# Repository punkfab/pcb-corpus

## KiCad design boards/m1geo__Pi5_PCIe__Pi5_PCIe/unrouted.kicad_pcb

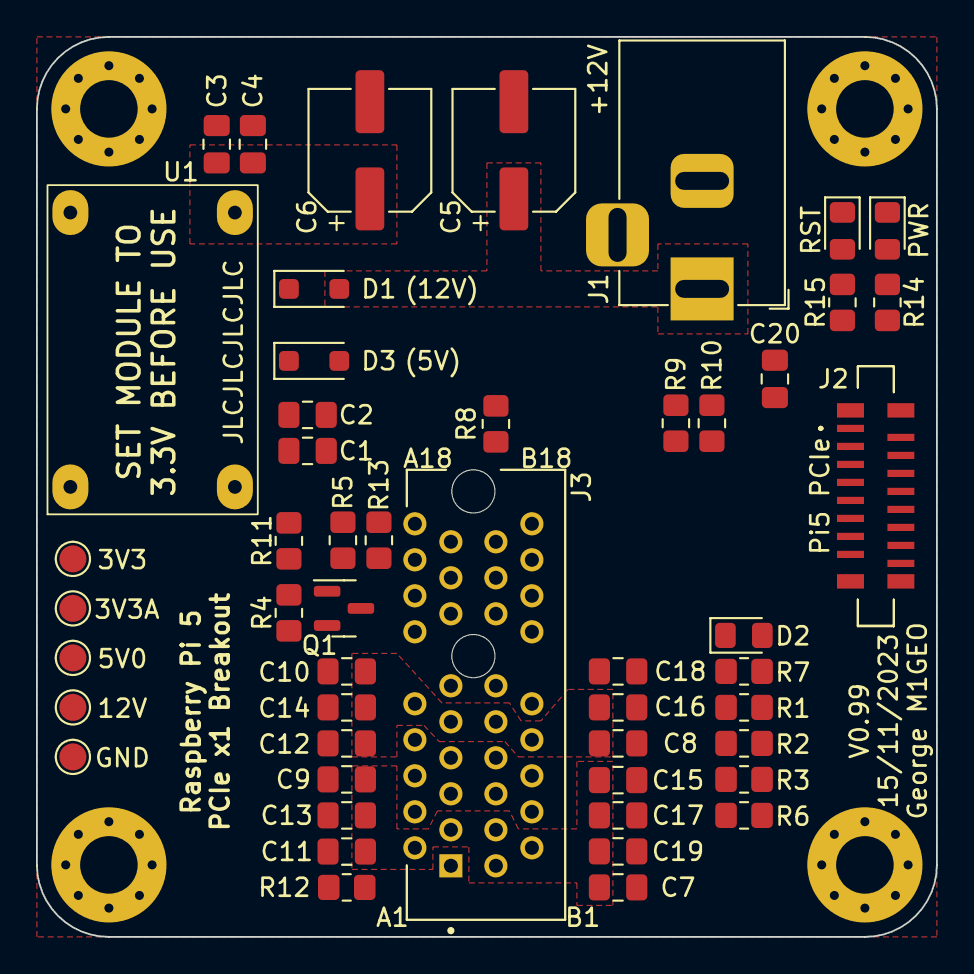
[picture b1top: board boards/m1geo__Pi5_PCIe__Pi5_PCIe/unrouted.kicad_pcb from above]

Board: 4 copper layers, 50.0 x 50.0 mm, 54 parts (0 on the bottom side), 24 nets, no tracks yet.

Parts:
C1, C3, C11, C12, C13, C14, C15, C16, C17, C18, C19, C20: 100n; C_0805_2012Metric_Pad1.18x1.45mm_HandSolder
C2, C4, C7, C8, C9, C10: 10u; C_0805_2012Metric_Pad1.18x1.45mm_HandSolder
C5, C6: 150u; CP_Elec_6.3x7.7
D1: (12V); D_SOD-123F
D2: DNF; D_0805_2012Metric_Pad1.15x1.40mm_HandSolder
D3: (5V); D_SOD-123F
D4: PWR; LED_0805_2012Metric_Pad1.15x1.40mm_HandSolder
D5: RST; LED_0805_2012Metric_Pad1.15x1.40mm_HandSolder
H1, H2, H3, H4: MountingHole_Pad; MountingHole_3.2mm_M3_Pad_Via
J1: 12V IN; BarrelJack_Horizontal
J2: Pi5 PCIe; 687316124422
J3: 10018783-11200TLF; AMPHENOL_10018783-11200TLF
Q1: BS170F; SOT-23
R1, R2, R3: DNF; R_0805_2012Metric_Pad1.20x1.40mm_HandSolder
R4, R6, R7, R8, R9, R10, R13: 10k; R_0805_2012Metric_Pad1.20x1.40mm_HandSolder
R5, R11, R12: 0; R_0805_2012Metric_Pad1.20x1.40mm_HandSolder
R14, R15: 1k; R_0805_2012Metric_Pad1.20x1.40mm_HandSolder
TP1: 3V3; TestPoint_Pad_D1.5mm
TP2: 3V3A; TestPoint_Pad_D1.5mm
TP3: 5V0; TestPoint_Pad_D1.5mm
TP4: 12V; TestPoint_Pad_D1.5mm
TP5: GND; TestPoint_Pad_D1.5mm
U1: Mini360; Mini360_step-down

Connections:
+3.3VA: C18.1, J3.B10, R6.2, R7.2, R8.2, R9.2, R10.2, R11.1, R13.2, TP2.1
+3V3: C3.1, C4.1, C6.1, C8.1, C10.1, C12.1, C14.1, C16.1, J3.A9, J3.A10, J3.B8, R11.2, R14.1, TP1.1, U1.4 (OUT+)
+5V: C20.1, D3.2 (A), J2.15 (Pin_17), J2.16 (Pin_18), TP3.1
+12V: C5.1, C7.1, C9.1, C11.1, C13.1, C15.1, C17.1, C19.1, D1.2 (A), J1.1, J3.A2, J3.A3, J3.B1, J3.B2, J3.B3, TP4.1
/PRSNT1#: J3.A1, R12.1
/REG_IN: C1.1, C2.1, D1.1 (K), D3.1 (K), U1.2 (IN+)
GND: C1.2, C2.2, C3.2, C4.2, C5.2, C6.2, C7.2, C8.2, C9.2, C10.2, C11.2, C12.2, C13.2, C14.2, C15.2, C16.2, C17.2, C18.2, C19.2, C20.2, D4.1 (K), D5.1 (K), H1.1, H2.1, H3.1, H4.1, J1.2, J1.3, J2.5 (Pin_7), J2.8 (Pin_10), J2.11 (Pin_13), J2.14 (Pin_16), J2.MP1, J2.MP2, J2.MP3, J2.MP4, J3.A4, J3.A12, J3.A15, J3.A18, J3.B4, J3.B7, J3.B13, J3.B16, J3.B18, Q1.2 (S), R4.2, R12.2, TP5.1, U1.1 (IN-), U1.3 (OUT-)
unnamed: D4.2 (A), R14.2
unnamed: D5.2 (A), R15.2
unnamed: Q1.1 (G), R4.1, R5.1
PCIE_CLKN: J2.12 (Pin_14), J3.A14
PCIE_CLKP: J2.13 (Pin_15), J3.A13
PCIE_CLKREQ#: J3.B12, R3.1, R6.1
PCIE_PERST#: J3.A11, Q1.3 (D), R13.1
PCIE_PRSNT2#: J3.B17, R2.1, R8.1
PCIE_RX0N: J2.9 (Pin_11), J3.A17
PCIE_RX0P: J2.10 (Pin_12), J3.A16
PCIE_SMCLK: J2.4 (Pin_6), J3.B5, R9.1
PCIE_SMDAT: D2.2 (A), J2.3 (Pin_5), J3.B6, R10.1
PCIE_TX0N: J2.6 (Pin_8), J3.B15
PCIE_TX0P: J2.7 (Pin_9), J3.B14
PCIE_WAKE#: D2.1 (K), J3.B11, R1.1, R7.1
RESET: J2.1 (Pin_3), R5.2, R15.1
UNKNOWN?!: J2.2 (Pin_4), R1.2, R2.2, R3.2

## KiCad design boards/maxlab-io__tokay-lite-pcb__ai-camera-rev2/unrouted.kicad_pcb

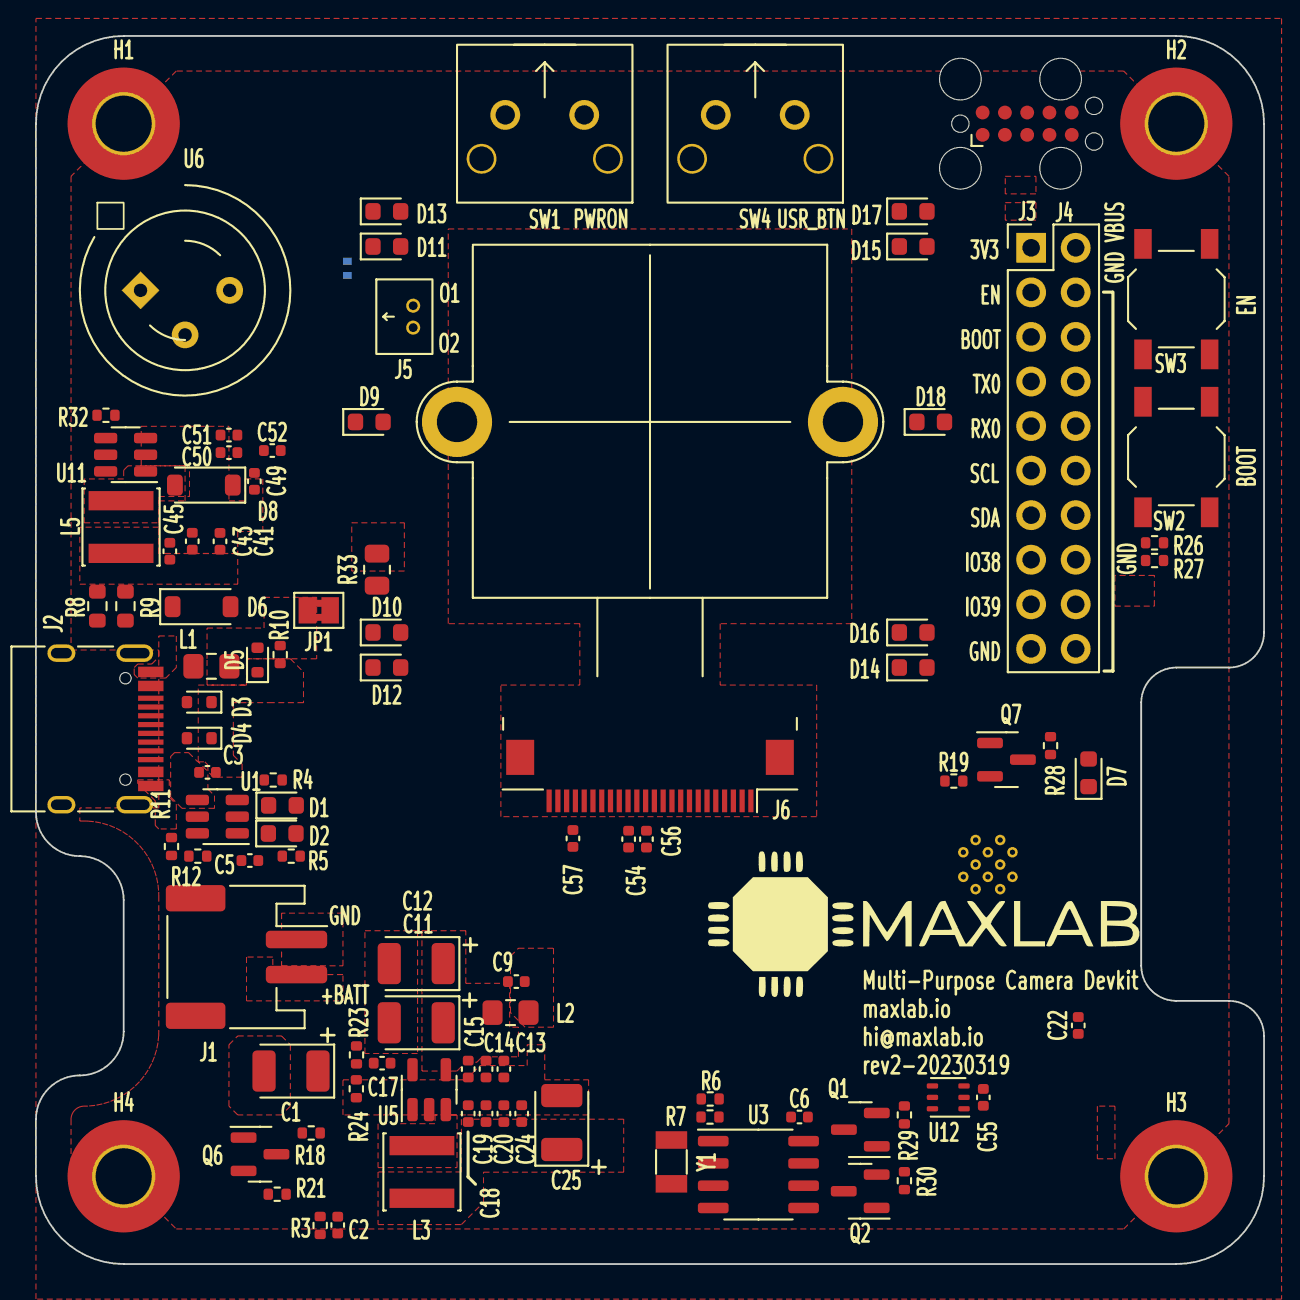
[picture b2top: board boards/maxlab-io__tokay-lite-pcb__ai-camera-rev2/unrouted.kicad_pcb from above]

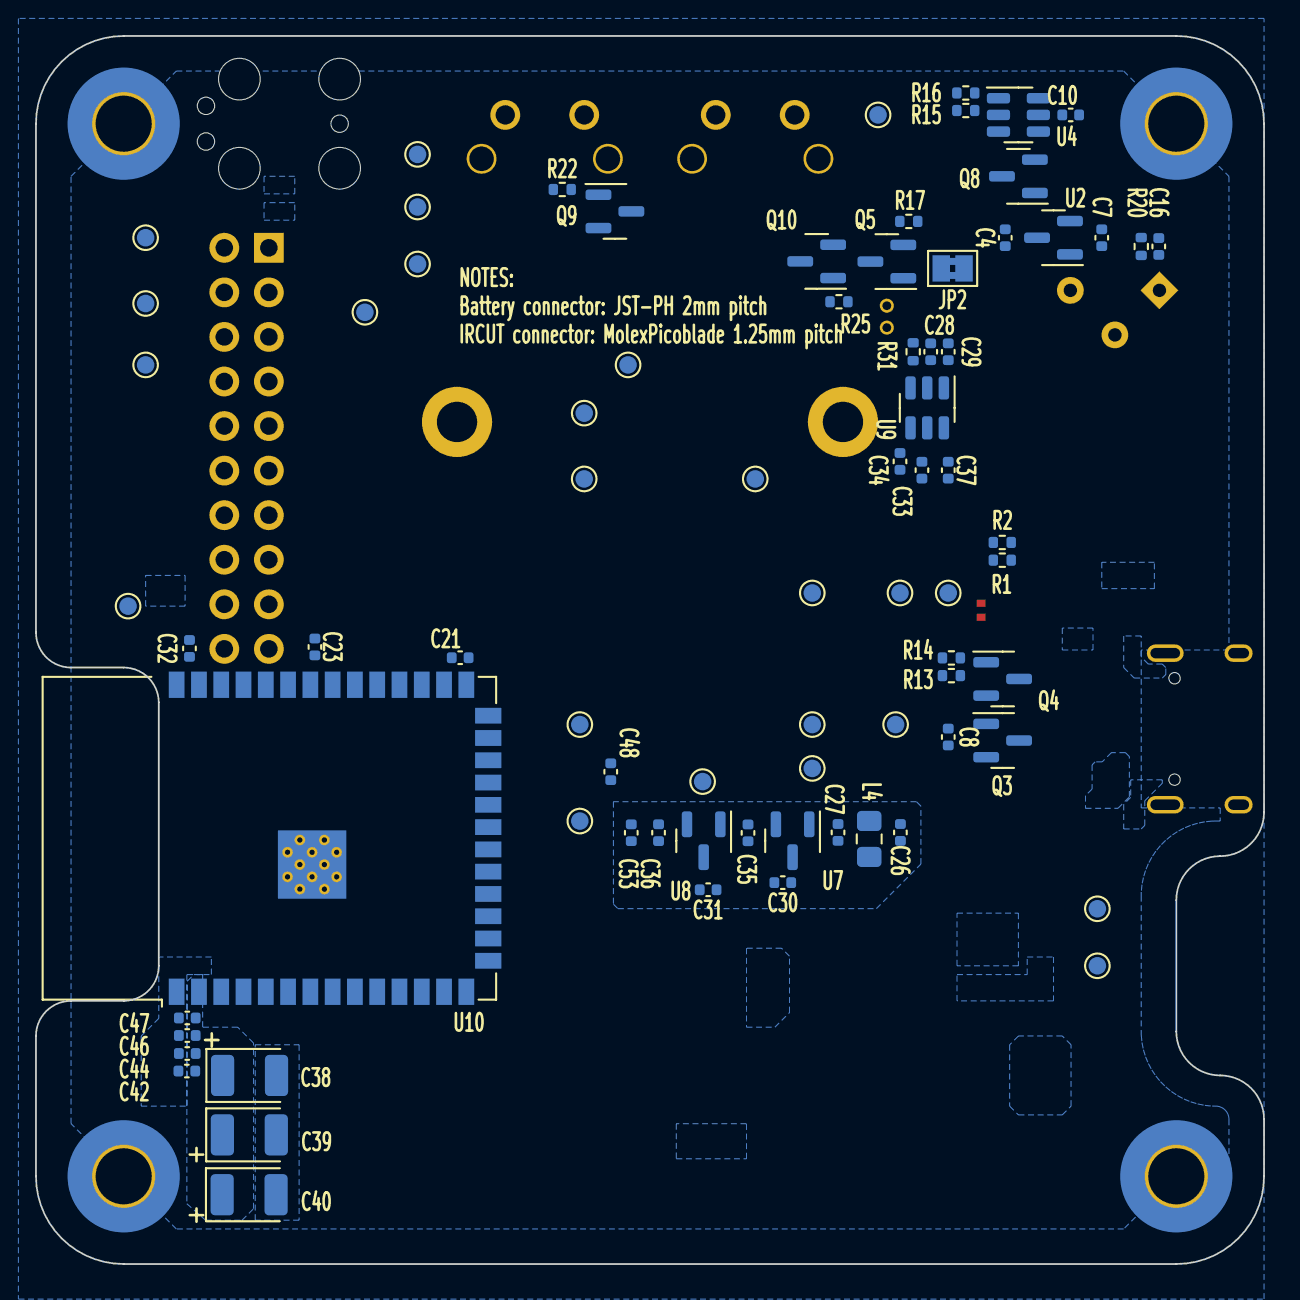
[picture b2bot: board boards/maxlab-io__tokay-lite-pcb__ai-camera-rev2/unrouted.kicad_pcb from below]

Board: 4 copper layers, 70.0 x 70.0 mm, 176 parts (77 on the bottom side), 84 nets, no tracks yet.

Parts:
C1, C11, C12, C25, C38, C39, C40: 100u_CASE-B-3528_TAJB107K006RNJ; CP_EIA-3528-15_AVX-H
C2, C3, C4, C5, C6, C7, C8, C9, C10, C13, C14, C15, C16, C18, C19, C20, C21, C22, C23, C24, C26, C27, C28, C29, C30, C31, C32, C33, C34, C35, C36, C37, C41, C42, C43, C44, C45, C46, C47, C49, C50, C51, C52, C53, C54, C55, C56, C57: 10u_0402_CL05A105KA5NQNC; C_0402_1005Metric
C17, C48: 22p_0402_0402CG220J500NT; C_0402_1005Metric
D1, D7: 0603_RED_KT-0603R; LED_0603_1608Metric
D2: 0603_GREEN_19-217/GHC-YR1S2/3T; LED_0603_1608Metric
D3, D4, D5: SOD-523_BSD5C051L; D_SOD-523
D6, D8: B5819W-SL_SOD-123; D_SOD-123
D9, D10, D11, D12, D13, D14, D15, D16, D17, D18: 0603_IR_850nm_E6C0603IRAC1UDA; LED_0603_1608Metric
H1, H2, H3, H4: MountingHole_Pad; MountingHole_3.2mm_M3_Pad_TopBottom
J1: Conn-01x02_P2mm_NONAME_JST-PH_C47647; JST_PH_S2B-PH-SM4-TB_1x02-1MP_P2.00mm_Horizontal
J2: TYPE-C-31-M-12; USB_C_Receptacle_HRO_TYPE-C-31-M-12
J3: MAXLAB; Tag-Connect_TC2050-IDC-FP_2x05_P1.27mm_Vertical
J4: Conn-02x10_P2.54mm_B-2100S20P-B110; PinHeader_2x10_P2.54mm_Vertical
J5: Conn-01x02_P1.25mm_10114829-10102LF; 10114829-10102LF
J6: Conn_01x24_FFC_0.5mm_AFC01-S24FCC-00; Jushuo_AFC01-S24FCC-00_1x24-1MP_P0.50_Horizontal
JP1: USB_PWR; SolderJumper-2_P1.3mm_Bridged2Bar_Pad1.0x1.5mm
JP2: PIR; SolderJumper-2_P1.3mm_Bridged2Bar_Pad1.0x1.5mm
L1, L2, L4: 0805_FB_220R@100MHz_BLM21PG221SN1D; L_0805_2012Metric_Pad1.15x1.40mm_HandSolder
L3, L5: 10u_SWPA4030S100MT; L_Sunlord_SWPA40xxS
Q1, Q2, Q5, Q7, Q9, Q10: 2N7002; SOT-23
Q3, Q4, Q6, Q8: AO3401A; SOT-23
R1, R2, R23: 976k_0402_0402WGD9763TCE; R_0402_1005Metric
R3, R13, R15, R16, R17, R18, R19, R21, R22, R24, R25, R31, R32: 215k_0402_0402WGD2153TCE; R_0402_1005Metric
R4, R5, R28: 1k_0402_0402WGF1001TCE; R_0402_1005Metric
R6, R7, R10, R11, R12, R14, R20, R26, R27, R29, R30: 10k_0402_0402WGF1002TCE; R_0402_1005Metric
R8, R9: 5.1k_0603_0603WAF5101T5E; R_0603_1608Metric
R33: 2.43R_0805_0805W8F243KT5E; R_0805_2012Metric
SW1, SW4: SW_PB_90deg_K2-1102AQ-H4CW-01
SW2, SW3: SW_PB_TS-1187A-B-A-B; SW_SPST_TL3342
TP1, TP2, TP3, TP4, TP5, TP6, TP7, TP8, TP9, TP10, TP11, TP12, TP13, TP14, TP15, TP16, TP17, TP18, TP19, TP20, TP21, TP22, TP23, TP24: TestPoint; TestPoint_Pad_D1.0mm
U1: TP4057-42-SOT26-R; SOT-23-6
U2, U7: XC6206-2.8V; SOT-23
U3: PCF85063AT_SO8; SO-8_3.9x4.9mm_P1.27mm
U4: SOT-23-6_SN74LVC1G373DBVR_TI; SOT-23-6
U5: SY8089AAAC; SOT-23-5
U6: PIR_AS312; AS312
U8: RT9166-12GVL; SOT-23
U9: AP1511B; SOT-23-6
U10: ESP32-S3-WROOM-1-N16R8; ESP32-S3-WROOM-1
U11: MT9284-28J; SOT-23-6
U12: LTR-303ALS-01; Lite-On_LTR-303ALS-01
Y1: 32.768kHz_Q13FC1350000400; Crystal_SMD_3215-2Pin_3.2x1.5mm

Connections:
+1V2: C36.1, C54.2, J6.15, TP16.1, U8.2 (VO)
+2V8: C35.1, C57.2, J6.21, TP18.1, U7.2 (VO)
+3.3VA: C27.1, C30.1, C31.1, C53.1, C56.2, J6.14, L4.2, U7.3 (VI), U8.3 (VI)
+3V3: C17.1, C18.2, C19.2, C20.2, C24.2, C25.1, C26.1, C33.2, C34.2, C37.2, C38.1, C39.1, C40.1, C42.1, C44.1, C46.1, C47.1, C55.1, J3.2, J4.1, L3.2, L4.1, Q1.1 (G), Q2.1 (G), R23.1, R26.2, R27.2, R29.1, R30.1, TP22.1, U9.5 (VDD), U10.2 (3V3), U12.1 (VDD)
+5V: C3.2, D5.2 (A2), JP1.2 (B), L1.2, R4.1, R5.1, R10.1, TP23.1, U1.4 (V_{cc})
+BATT: C1.1, C5.1, J1.2, Q3.3 (D), R1.1, TP19.1, U1.3 (BAT)
/BATT_DETECT: C32.1, R1.2, R2.1, TP11.1, U10.39 (GPIO1/TOUCH1/ADC1_CH0)
/CAM.D2: J6.6, U10.7 (GPIO7/TOUCH7/ADC1_CH6)
/CAM.D3: J6.4, U10.5 (GPIO5/TOUCH5/ADC1_CH4)
/CAM.D4: J6.3, U10.4 (GPIO4/TOUCH4/ADC1_CH3)
/CAM.D5: J6.5, U10.6 (GPIO6/TOUCH6/ADC1_CH5)
/CAM.D6: J6.7, U10.8 (GPIO15/U0RTS/ADC2_CH4/XTAL_32K_P)
/CAM.D7: J6.9, U10.10 (GPIO17/U1TXD/ADC2_CH6)
/CAM.D8: J6.11, U10.11 (GPIO18/U1RXD/ADC2_CH7/CLK_OUT3)
/CAM.D9: J6.13, U10.20 (GPIO12/TOUCH12/ADC2_CH1/FSPICLK/FSPIIO6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)
/CAM.HREF: J6.16, U10.33 (MTDO/GPIO40/CLK_OUT2)
/CAM.MCLK: J6.12, U10.12 (GPIO8/TOUCH8/ADC1_CH7/SUBSPICS1)
/CAM.PCLK: C48.1, J6.8, U10.9 (GPIO16/U0CTS/ADC2_CH5/XTAL_32K_NH5)
/CAM.PWDN: J6.17, U10.17 (GPIO9/TOUCH9/ADC1_CH8/FSPIHD/SUBSPIHD)
/CAM.RST: J6.19, U10.19 (GPIO11/TOUCH11/ADC2_CH0/FSPID/FSPIIO5/S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)
/CAM.SCL: J4.11, J6.20, Q1.2 (S), R29.2, U10.15 (GPIO3/TOUCH3/ADC1_CH2), U12.4 (SCL)
/CAM.SDA: J4.13, J6.22, Q2.2 (S), R30.2, U10.21 (GPIO13/TOUCH13/ADC2_CH2/FSPIQ/FSPIIO7/S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), U12.6 (SDA)
/CAM.VSYNC: J6.18, U10.18 (GPIO10/TOUCH10/ADC1_CH9/FSPICS0/FSPIIO4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)
/ESP_BOOT: C21.2, J3.6, J4.5, R26.1, SW2.2, TP2.1, U10.27 (GPIO0/BOOT)
/ESP_EN: C22.2, J3.5, J4.3, R27.1, SW3.2, TP1.1, U10.3 (EN)
/IO38: J4.15, U10.31 (GPIO38/FSPIWP/SUBSPIWP)
/IO39: J4.17, U10.32 (MTCK/GPIO39/CLK_OUT3/SUBSPICS1)
/IRCUT_CTRL: R31.2, TP10.1, U9.3 (FBC), U10.25 (GPIO48/SPICLK_N/SUBSPICLK_N_DIFF)
/IRLED_PWM: R32.2, TP14.1, U10.16 (GPIO46), U11.4 (EN)
/PIR_CTRL_D: R15.2, TP8.1, U4.3 (D), U10.23 (GPIO21)
/PIR_CTRL_LE: R16.2, TP7.1, U4.1 (LE), U10.26 (GPIO45)
/PIR_OUT: Q10.3 (D), U10.24 (GPIO47/SPICLK_P/SUBSPICLK_P_DIFF)
/PWRON_DET: Q9.1 (G), R22.2, SW1.2, U10.38 (GPIO2/TOUCH2/ADC1_CH1)
/PWR_EN: Q7.1 (G), R19.2, TP12.1, U10.22 (GPIO14/TOUCH14/ADC2_CH3/FSPIWP/FSPIDQS/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)
/PWR_PIR: C7.1, C10.1, C16.1, R20.1, SW1.1, TP13.1, U2.2 (VO), U4.5 (VCC), U6.1 (VDD)
/RXD0: J3.8, J4.9, TP5.1, U10.36 (U0RXD/GPIO44/CLK_OUT2)
/TXD0: J3.7, J4.7, TP4.1, U10.37 (U0TXD/GPIO43/CLK_OUT1)
/UD+: D4.2 (A2), J2.A6 (D+), J2.B6 (D+), U10.14 (GPIO20/U1CTS/ADC2_CH9/CLK_OUT1/USB_D+)
/UD-: D3.2 (A2), J2.A7 (D-), J2.B7 (D-), U10.13 (GPIO19/U1RTS/ADC2_CH8/CLK_OUT2/USB_D-)
/USR_BTN: C23.2, SW4.2, U10.34 (MTDI/GPIO41/CLK_OUT1)
/USR_LED: R28.1, U10.35 (MTMS/GPIO42)
GND: C1.2, C2.1, C3.1, C4.1, C5.2, C6.2, C7.2, C9.1, C10.2, C11.2, C12.2, C13.1, C14.2, C15.1, C16.2, C18.1, C19.1, C20.1, C21.1, C22.1, C23.1, C24.1, C25.2, C26.2, C27.2, C28.2, C29.2, C30.2, C31.2, C32.2, C33.1, C34.1, C35.2, C36.2, C37.1, C38.2, C39.2, C40.2, C41.1, C42.2, C43.2, C44.2, C45.1, C46.2, C47.2, C48.2, C49.2, C50.1, C51.1, C52.1, C53.2, C54.1, C55.2, C56.1, C57.1, D3.1 (A1), D4.1 (A1), D5.1 (A1), D7.1 (K), J1.1, J2.A1 (GND), J2.A12 (GND), J2.B1 (GND), J2.B12 (GND), J3.3, J3.4, J4.4, J4.6, J4.8, J4.10, J4.12, J4.14, J4.16, J4.18, J4.19, J4.20, J6.10, J6.23, Q5.2 (S), Q7.2 (S), Q9.2 (S), Q10.2 (S), R2.2, R3.2, R8.2, R9.2, R10.2, R11.2, R12.2, R13.2, R15.1, R16.1, R17.1, R19.1, R21.2, R22.1, R24.2, R25.1, R31.1, R32.1, R33.2, SW2.1, SW3.1, SW4.1, TP3.1, TP6.1, TP9.1, TP15.1, TP17.1, TP20.1, TP24.1, U1.2 (GND), U2.1 (GND), U3.4 (VSS), U4.2 (G), U4.6 (~OE), U5.2 (GND), U6.3 (VSS), U7.1 (GND), U8.1 (GND), U9.2 (GND), U10.1 (GND), U10.40 (GND), U10.41 (GND), U11.2 (GND), U12.3 (GND)
GNDPWR: C2.2, H1.1, H2.1, H3.1, H4.1, J2.S1 (SHIELD), R3.1
unnamed: D1.2 (A), R4.2
unnamed: D1.1 (K), U1.1 (~CHRG)
unnamed: D2.2 (A), R5.2
unnamed: D2.1 (K), U1.5 (~STDBY)
unnamed: D6.2 (A), JP1.1 (A), R14.1
unnamed: D7.2 (A), R28.2
unnamed: D8.2 (A), L5.2, U11.1 (SW)
unnamed: C49.1, C50.2, C51.2, C52.2, D8.1 (K), D9.2 (A), U11.5 (OV)
unnamed: D10.2 (A), D12.1 (K)
unnamed: D10.1 (K), R33.1, U11.3 (FB)
unnamed: D9.1 (K), D11.2 (A)
unnamed: D11.1 (K), D13.2 (A)
unnamed: D12.2 (A), D14.1 (K)
unnamed: D13.1 (K), D15.2 (A)
unnamed: D14.2 (A), D16.1 (K)
unnamed: D15.1 (K), D17.2 (A)
unnamed: D16.2 (A), D18.1 (K)
unnamed: D17.1 (K), D18.2 (A)
unnamed: J2.A5 (CC1), R8.1
unnamed: J2.B5 (CC2), R9.1
unnamed: J2.A4 (VBUS), J2.A9 (VBUS), J2.B4 (VBUS), J2.B9 (VBUS), L1.1
unnamed: J5.1, U9.6 (OUT2)
unnamed: J5.2, U9.4 (OUT1)
unnamed: JP2.1 (A), Q8.3 (D), Q10.1 (G), R25.2
unnamed: JP2.2 (B), Q5.1 (G), R17.2
unnamed: Q1.3 (D), R6.2, U3.6 (SCL)
unnamed: Q2.3 (D), R7.2, U3.5 (SDA)
unnamed: C8.1, Q3.1 (G), Q4.1 (G), R13.1, R14.2
unnamed: C8.2, Q3.2 (S), Q4.2 (S)
unnamed: Q5.3 (D), Q6.1 (G), Q7.3 (D), Q9.3 (D), R18.2, U3.3 (~INT)
unnamed: Q6.3 (D), R21.1, U5.1 (EN)
unnamed: C11.1, C12.1, C13.2, C14.1, C15.2, L2.2, Q6.2 (S), R18.1, U5.4 (IN)
unnamed: Q8.1 (G), R20.2, U4.4 (Q)
unnamed: Q8.2 (S), U6.2 (REL)
unnamed: R11.1, R12.1, U1.6 (PROG)
unnamed: U3.1 (OSCI), Y1.2
unnamed: U3.2 (OSCO), Y1.1
unnamed: C17.2, R23.2, R24.1, U5.5 (FB)
unnamed: L3.1, U5.3 (LX)
unnamed: C28.1, C29.1, U9.1 (CE)
VBUS: C4.2, C6.1, C9.2, C41.2, C43.1, C45.2, D6.1 (K), J3.1, J4.2, L2.1, L5.1, Q4.3 (D), R6.1, R7.1, TP21.1, U2.3 (VI), U3.8 (VDD), U11.6 (VIN)

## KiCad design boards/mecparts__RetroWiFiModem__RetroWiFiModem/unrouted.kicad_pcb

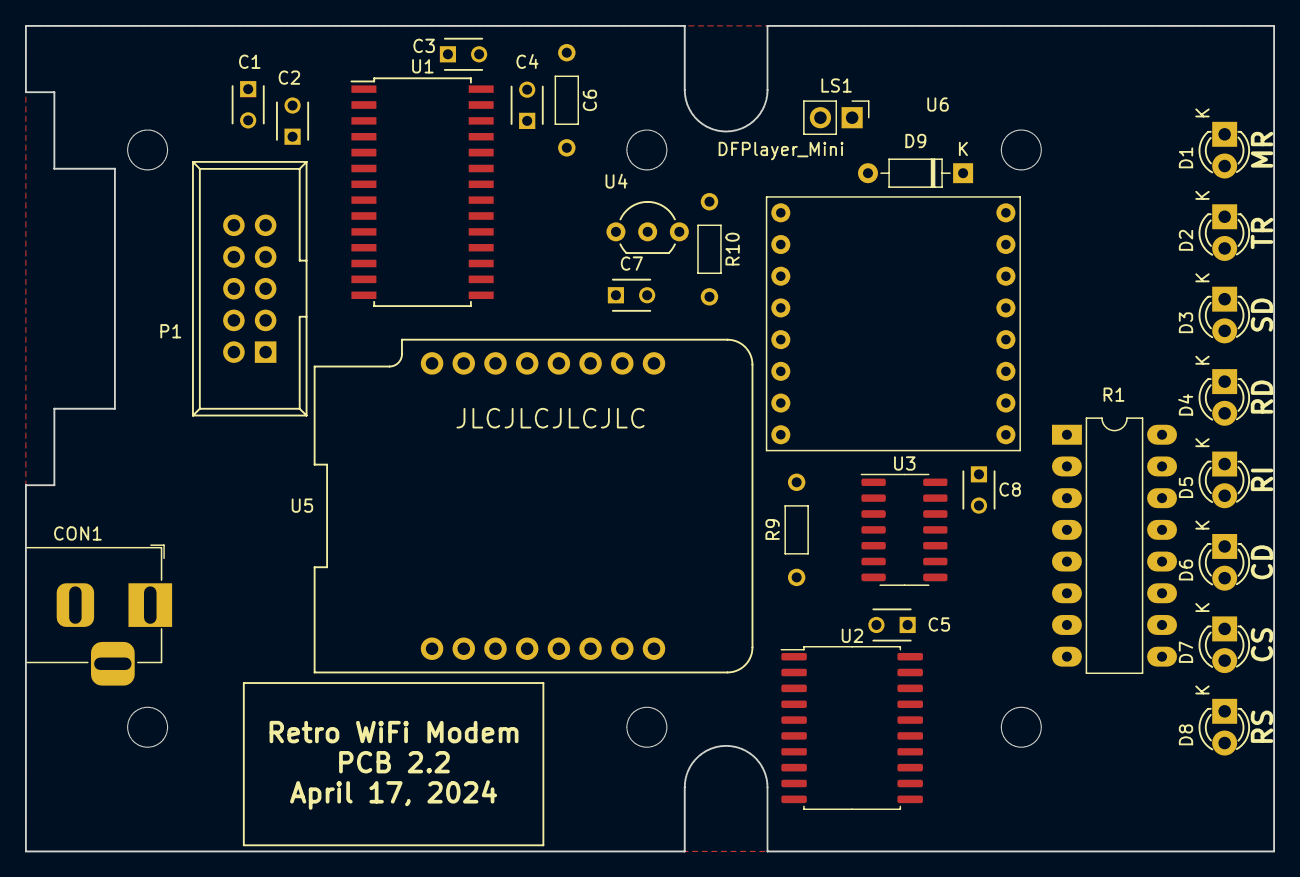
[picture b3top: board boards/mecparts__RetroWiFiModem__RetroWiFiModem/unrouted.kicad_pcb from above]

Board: 2 copper layers, 100.0 x 66.1 mm, 35 parts (0 on the bottom side), 48 nets, no tracks yet.

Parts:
C1, C2, C3, C4, C5, C8: 100nF; C_Disc_D3_P2.5
C6: 100nF; R3
C7: 1uF; C_Disc_D3_P2.5
CON1: BarrelJack_Horizontal
D1, D2, D3, D4, D5, D6, D7, D8: TLPR5600; LED-3MM
D9: 1N4148; D_DO-35_SOD27_P7.62mm_Horizontal
H1, H2, H3, H4, H5, H6: MountingHole; MountingHole_3.2mm
LS1: Speaker; PinHeader_1x02_P2.54mm_Vertical
P1: CONN_02X05; IDC_Header_Straight_10pins
R1: 560R; DIP-16_W7.62mm_LongPads
R9, R10: 10K; R3
U1: MAX3237CAI+; SOIC-28W_7.5x17.9mm_Pitch1.27mm
U2: 74HCT245; SOIC-20W_7.5x12.8mm_P1.27mm
U3: 74HC32; SOIC-14_3.9x8.7mm_P1.27mm
U4: L4931CZ33-AP; TO-92_Inline_Wide
U5: WeMos_mini; wemos-d1-mini-with-pin-header-and-connector
U6: DFPlayer_Mini; DFPlayerMini

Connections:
+3V3: C3.1, C4.1, C7.1, C8.1, R9.1, R10.1, U1.14 (SHDN), U1.26 (VCC), U3.14 (VCC), U4.1 (VO)
+5V: C5.1, CON1.1, D1.2 (A), D2.2 (A), D3.2 (A), D4.2 (A), D5.2 (A), D6.2 (A), D7.2 (A), D8.2 (A), U2.1 (A->B), U2.20 (VCC), U4.3 (VI), U5.1 (5V), U6.1 (VCC)
GND: C2.2, C4.2, C5.2, C7.2, C8.2, CON1.2, P1.9, U1.2 (GND), U1.15 (MBAUD), U2.10 (GND), U2.19 (CE), U3.4, U3.5, U3.7 (GND), U3.9, U3.10, U3.12, U3.13, U4.2 (GND), U5.2 (GND), U6.7 (GND), U6.10 (GND)
unnamed: C1.1, U1.1 (C2+)
unnamed: C1.2, U1.3 (C2-)
unnamed: C2.1, U1.4 (V-)
unnamed: C3.2, U1.27 (V+)
unnamed: C6.1, U1.28 (C1+)
unnamed: C6.2, U1.25 (C1-)
unnamed: D1.1 (K), R1.16 (R1.2)
unnamed: D2.1 (K), R1.15 (R1.2)
unnamed: D3.1 (K), R1.14 (R1.2)
unnamed: D4.1 (K), R1.13 (R1.2)
unnamed: D5.1 (K), R1.12 (R1.2)
unnamed: D6.1 (K), R1.11 (R1.2)
unnamed: D7.1 (K), R1.10 (R1.2)
unnamed: D8.1 (K), R1.9 (R1.2)
unnamed: D9.1 (K), U6.16 (BUSY)
unnamed: D9.2 (A), R10.2, U5.11 (D0)
unnamed: LS1.1, U6.8 (SPK-)
unnamed: LS1.2, U6.6 (SPK+)
unnamed: P1.1, U1.7 (T3OUT)
unnamed: P1.2, U1.10 (T4OUT)
unnamed: P1.3, U1.5 (T1OUT)
unnamed: P1.4, U1.9 (R2IN)
unnamed: P1.5, U1.8 (R1IN)
unnamed: P1.6, U1.6 (T2OUT)
unnamed: P1.7, U1.11 (R3IN)
unnamed: P1.8, U1.12 (T5OUT)
unnamed: R1.1 (R1.1), U2.18 (B0)
unnamed: R1.2 (R1.1), U2.17 (B1)
unnamed: R1.3 (R1.1), U2.16 (B2)
unnamed: R1.4 (R1.1), U2.15 (B3)
unnamed: R1.5 (R1.1), U2.14 (B4)
unnamed: R1.6 (R1.1), U2.13 (B5)
unnamed: R1.7 (R1.1), U2.12 (B6)
unnamed: R1.8 (R1.1), U2.11 (B7)
unnamed: R9.2, U1.13 (EN), U3.2, U5.12 (D5)
unnamed: U1.17 (T5IN), U2.6 (A4), U5.13 (D6)
unnamed: U1.18 (R3OUT), U2.3 (A1), U5.4 (D3)
unnamed: U1.19 (T4IN), U2.2 (A0), U5.5 (D2)
unnamed: U1.20 (R2OUT), U2.9 (A7), U5.14 (D7)
unnamed: U1.21 (R1OUT), U2.4 (A2), U5.7 (Rx)
unnamed: U1.22 (T3IN), U2.7 (A5), U5.6 (D1)
unnamed: U1.23 (T2IN), U2.8 (A6), U5.15 (D8)
unnamed: U1.24 (T1IN), U2.5 (A3), U3.3
unnamed: U3.1, U5.8 (Tx)
unnamed: U5.3 (D4), U6.2 (RX)

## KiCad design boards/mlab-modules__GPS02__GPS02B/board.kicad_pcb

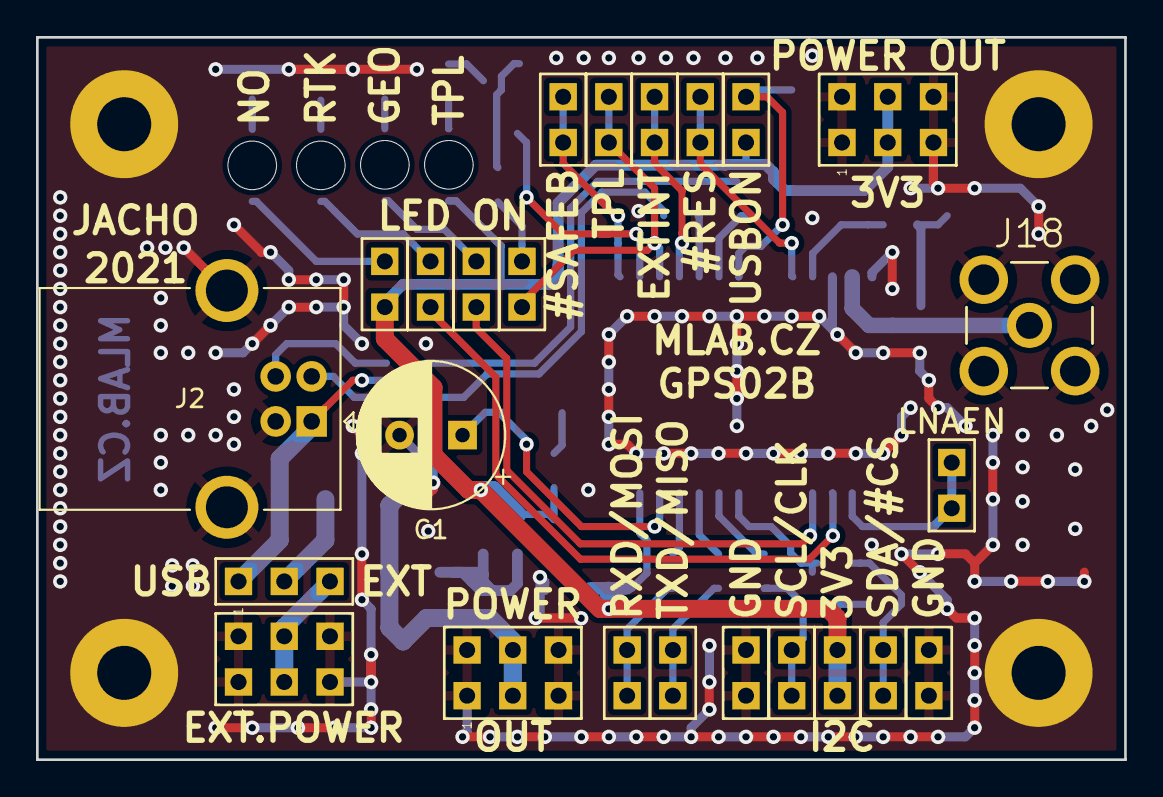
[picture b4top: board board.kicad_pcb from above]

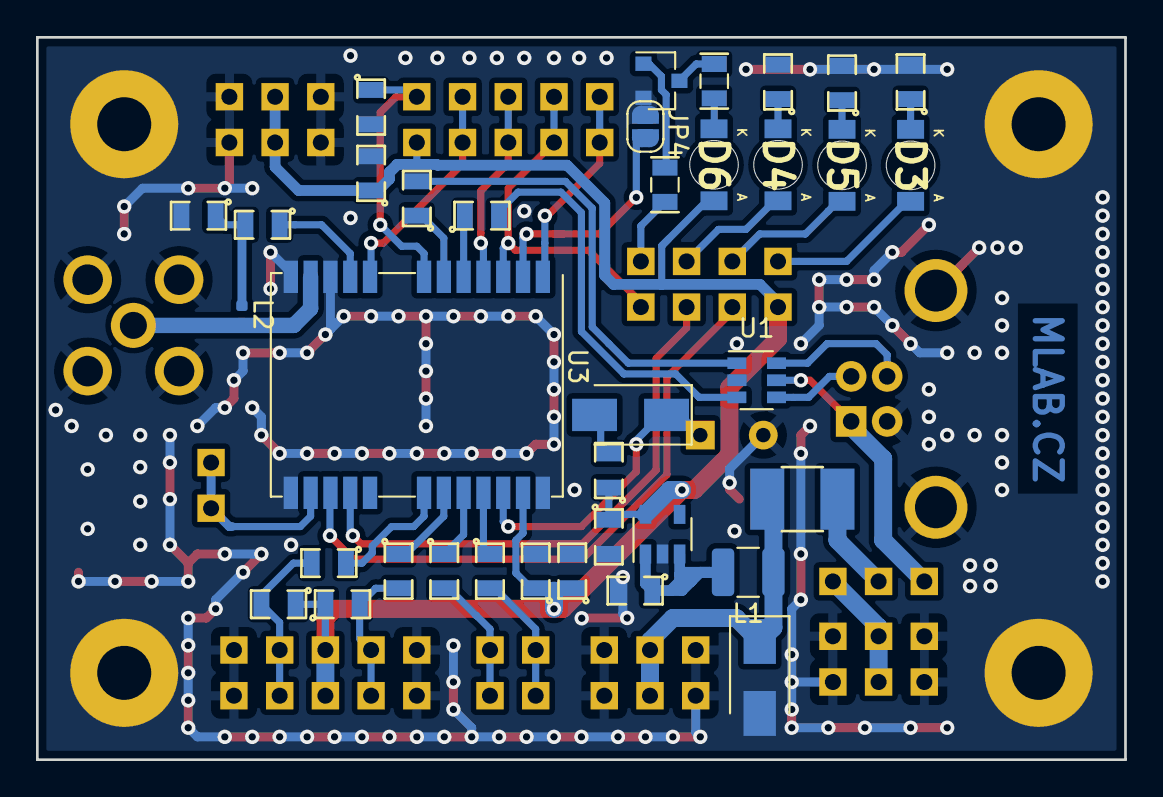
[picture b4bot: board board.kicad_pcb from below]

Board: 2 copper layers, 60.5 x 40.1 mm, 64 parts (36 on the bottom side), 45 nets.

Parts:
C1: 1F; CP_Radial_D8.0mm_P3.50mm
C2: 10uF; SMD-0805
C3, C5, C6: 1uF; SMD-0805
C4: 100nF; SMD-0805
C7: 47pF; SMD-0805
D1, D2: M4; D_SMA
D3: RED; LED_1206
D4, D5: YELLOW; LED_1206
D6: GREEN; LED_1206
F1: 750mA; 1812
J1, J3, J15: HEADER_2x03_PARALLEL; Straight_2x03
J2: USB_B; USB_B_OST_USB-B1HSxx_Horizontal
J4, J5, J6, J7, J8, J9, J10, J11, J12, J13, J14, J16: HEADER_2x01_PARALLEL; Straight_2x01
J18: SMA; SMA6251A13G50
JP1: Jumper_3_Bridged12; Straight_1x03
JP2, JP6: Jumper_2_Bridged; Straight_1x02
JP4: Jumper_2_Open; SolderJumper-2_P1.3mm_Open_RoundedPad1.0x1.5mm
JP7, JP8, JP9: Jumper_2_Open; Straight_1x02
L1: NL322522T-101K; L_1210_3225Metric
L2: 27nH; L_0402_1005Metric
M1, M2, M3, M4: HOLE; MountingHole_3mm
Q1: BC817-25; SOT-23
R1: 22R; SMD-0805
R2, R3, R15: 10k; SMD-0805
R4, R5, R6, R7, R8, R9: 33R; SMD-0805
R10, R12, R13: 620R; SMD-0805
R11: 10R; SMD-0805
R14, R16: 220R; SMD-0805
U1: USBLC6-2SC6; SOT-23-6
U2: MIC5504-3.3YM5; SOT-23-5
U3: NEO-M8P; ublox_NEO

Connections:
+3V3: C3.1, C4.1, C5.1, C6.1, D6.2 (A), J8.1, J8.2, J15.3, J15.4, JP2.2 (B), JP9.1 (A), R1.1, R2.1, R3.1, U2.5 (VOUT), U3.23 (VCC)
/#RESET: J13.1, J13.2, U3.8 (~RESET)
/#SAFEB: J12.1, J12.2, U3.1 (~SAFEBOOT)
/D+: J2.3 (D+), U1.6 (IO1)
/D-: J2.2 (D-), U1.4 (IO2)
/DM: R4.2, U1.3 (IO2)
/DP: R5.2, U1.1 (IO1)
/D_SEL: JP4.2 (B), U3.2 (D_SEL)
/EXTINT: J11.1, J11.2, U3.4 (EXTINT)
/GEO_STAT: D4.2 (A), JP8.2 (B)
/LNEN: J14.1, J14.2, U3.14 (LNA_EN)
/RTK_STAT: D5.2 (A), JP7.2 (B)
/RXD/MOSI: J5.1, J5.2, R7.2
/SCL/CLK: J7.1, J7.2, R3.2, R9.2
/SDA/#CS: J6.1, J6.2, R2.2, R8.2
/TIMEPULSE: JP6.2 (B), R14.1
/TXD/MISO: J4.1, J4.2, R6.2
/VBACKUP: C1.1, D1.1 (K), U3.22 (V_BCKP)
/VBUS: J2.1 (VBUS), JP1.1 (A), U1.5 (VBUS)
/VDD_USB: JP2.1 (A), R15.1, U3.7 (VDD_USB)
GND: C1.2, C2.2, C3.2, C4.2, C5.2, C6.2, C7.2, D2.2 (A), J1.1, J1.2, J1.5, J1.6, J2.4 (GND), J2.5 (Shield), J3.1, J3.2, J3.5, J3.6, J9.1, J9.2, J10.1, J10.2, J15.1, J15.2, J15.5, J15.6, J18.2, JP4.1 (A), M1.1, M2.1, M3.1, M4.1, Q1.2 (E), R10.2, R12.2, R13.2, R15.2, U1.2 (GND), U2.2 (GND), U3.10 (GND), U3.12 (GND), U3.13 (GND), U3.24 (GND)
unnamed: C2.1, L1.2, U2.1 (VIN), U2.3 (EN)
unnamed: C7.1, L2.1, R11.2
unnamed: D1.2 (A), R1.2
unnamed: D2.1 (K), F1.2, J3.3, J3.4, L1.1
unnamed: D3.1 (K), R10.1
unnamed: D3.2 (A), JP9.2 (B)
unnamed: D4.1 (K), R12.1
unnamed: D5.1 (K), R13.1
unnamed: D6.1 (K), R16.2
unnamed: F1.1, JP1.2 (C)
unnamed: J1.3, J1.4, JP1.3 (B)
unnamed: J16.1, J16.2, JP6.1 (A), U3.3 (TIMEPULSE)
unnamed: J18.1, L2.2, U3.11 (RF_IN)
unnamed: JP7.1 (A), U3.15 (RTK_STAT)
unnamed: JP8.1 (A), U3.16 (GEOFENCE_STAT)
unnamed: Q1.1 (B), R14.2
unnamed: Q1.3 (C), R16.1
unnamed: R4.1, U3.5 (USB_DM)
unnamed: R5.1, U3.6 (USB_DP)
unnamed: R6.1, U3.20 (TXD/SPI_MISO)
unnamed: R7.1, U3.21 (RXD/SPI_MOSI)
unnamed: R8.1, U3.18 (SDA/~SPI_CS)
unnamed: R9.1, U3.19 (SCL/SPI_CLK)
unnamed: R11.1, U3.9 (VCC_RF)

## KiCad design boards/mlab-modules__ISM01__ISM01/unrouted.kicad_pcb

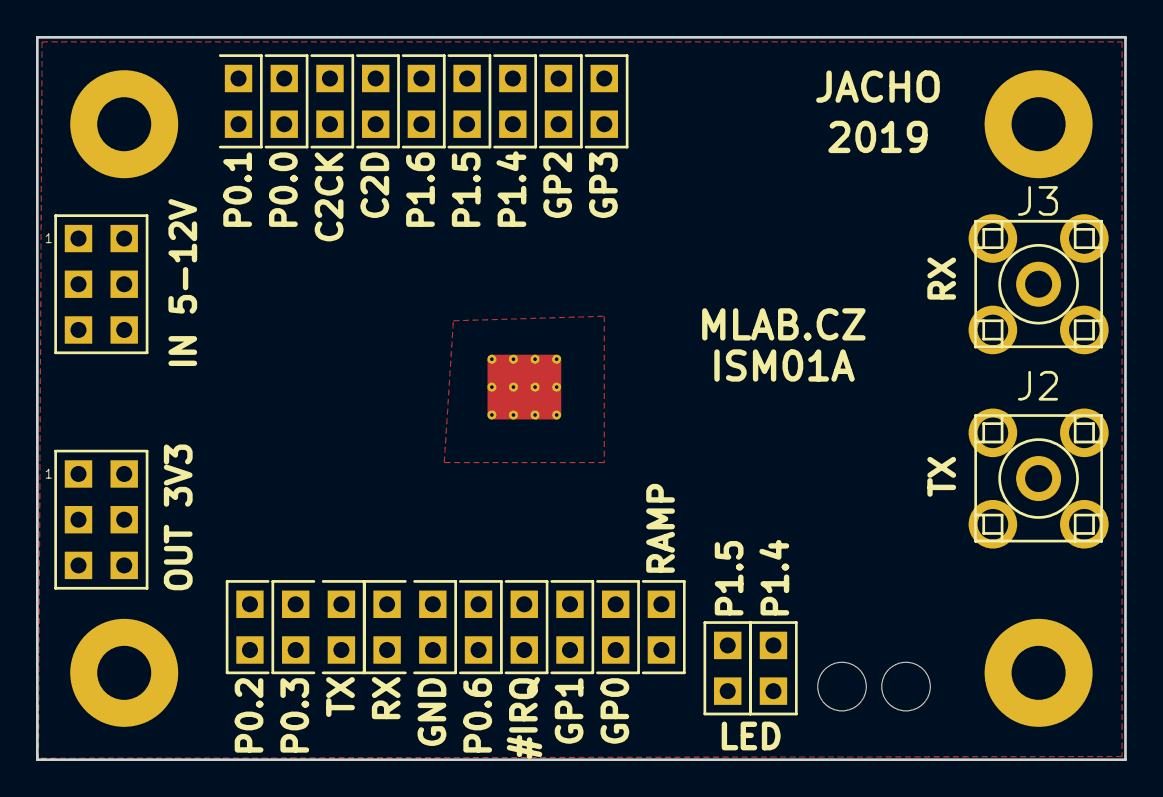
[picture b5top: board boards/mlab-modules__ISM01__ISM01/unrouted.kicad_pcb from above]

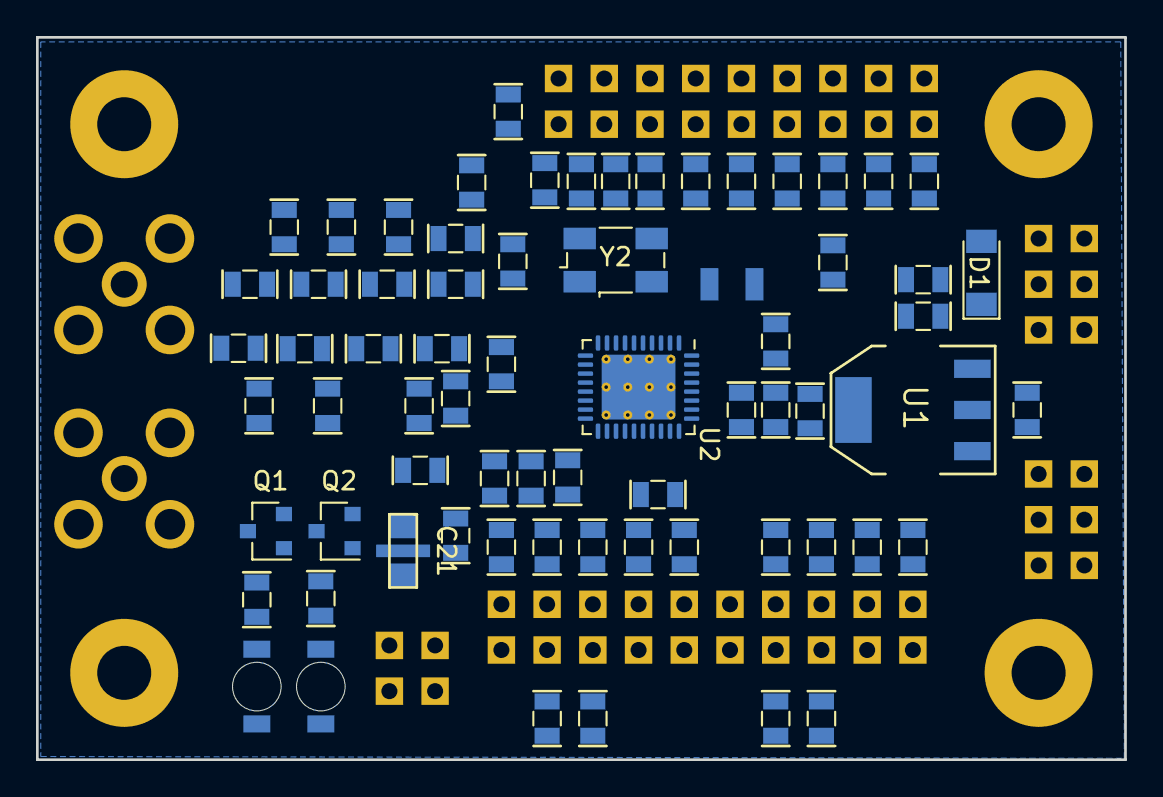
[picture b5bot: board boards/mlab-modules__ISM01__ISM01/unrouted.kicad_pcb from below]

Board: 2 copper layers, 60.5 x 40.1 mm, 98 parts (69 on the bottom side), 63 nets, no tracks yet.

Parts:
C1, C3, C5, C18, C20: 10uF; SMD-0805
C2, C16, C19: 100nF; SMD-0805
C4, C6: 6.8pf; SMD-0805
C7, C8: 15pF; SMD-0805
C9, C10, C11: 8,2pF; SMD-0805
C12: 2.7pF; SMD-0805
C13: 5.1pF; SMD-0805
C14, C22, C23, C25, C26, C27, C28: 10nF; SMD-0805
C15: 33pF; SMD-0805
C17: 100pF; SMD-0805
C21: NFM21PC105; FIR1
D1: M4; Diode-MiniMELF_Standard
D2: RED; LED_1206
D3: GREEN; LED_1206
J1, J4: JUMP_3X2; Straight_2x03
J2, J3: SMA; SMA6251A13G50
J6, J7, J8, J9, J10, J11, J12, J13, J14, J15, J16, J17, J18, J19, J20, J21, J22, J23, J26: HEADER_2x01_PARALLEL; Straight_2x01
J24, J25: HEADER_1x02; Straight_1x02
L1, L2: 0R; SMD-0805
L3, L4, L5, L6: 18nH; SMD-0805
L7: 39nH; SMD-0805
L8: 220nH; SMD-0805
L9, L10: 56nH; SMD-0805
M1, M2, M3, M4: HOLE; MountingHole_3mm
Q1, Q2: BC817; SOT-23
R1, R21: 0R; SMD-0805
R2, R3, R4, R5, R6, R7, R8, R9, R10, R11, R12, R13, R14, R15, R16, R17, R18, R19: 33R; SMD-0805
R20: 1k; SMD-0805
R22, R23: 150R; SMD-0805
U1: LM1117; SOT-223
U2: Si1060-A-GM; QFN-36-1EP_5x6mm_P0.5mm_EP3.6x4.1mm_ThermalVias
Y1: ABS07-120-32.768KHZ; ABS07
Y2: ABM3B-30.000MHZ-10-1-U-T; Crystal_SMD_Abracon_ABM3B-4Pin_5.0x3.2mm

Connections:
+3V3: C3.1, C5.1, C14.1, C16.1, C18.1, C21.3, D2.2, D3.2, J4.3, J4.4, R1.1, R20.1, U1.2, U1.4, U2.33
/#IRQ: J19.1, J19.2, R15.1
/#IRQ_1: R15.2, R21.1, U2.23
/#RST_1: R14.2, R20.2, U2.36
/#RST_C2CK: J18.1, J18.2, R14.1
/GPIO0: C22.1, J20.1, J20.2, R16.1
/GPIO1: C23.1, J21.1, J21.2, R17.1
/GPIO2: C25.1, J22.1, J22.2, R18.1
/GPIO3: C26.1, J23.1, J23.2, R19.1
/P0.0: J16.1, J16.2, R12.1
/P0.1: J15.1, J15.2, R11.1
/P0.1_1: R11.2, R21.2, U2.29
/P0.2: J14.1, J14.2, R10.1
/P0.3: J13.1, J13.2, R9.1
/P0.6: J10.1, J10.2, R6.1
/P1.4: J9.1, J9.2, J24.2, R5.1
/P1.5: J8.1, J8.2, J25.2, R4.1
/P1.6: J7.1, J7.2, R3.1
/P2.7C2D: J6.1, J6.2, R2.1
/RX: C27.1, J11.1, J11.2, R7.1
/TX: C28.1, J12.1, J12.2, R8.1
/TXRAMP: J17.1, J17.2, R13.1
GND: C1.2, C2.2, C3.2, C4.2, C5.2, C6.2, C7.2, C8.2, C9.2, C10.2, C13.2, C14.2, C15.2, C16.2, C17.2, C18.2, C19.2, C20.2, C21.2, C22.2, C23.2, C25.2, C26.2, C27.2, C28.2, D1.2, J1.1, J1.2, J1.5, J1.6, J2.2, J3.2, J4.1, J4.2, J4.5, J4.6, J26.1, J26.2, M1.1, M2.1, M3.1, M4.1, Q1.2, Q2.2, U1.1, U2.9, U2.14, U2.15, U2.17, U2.31, U2.37, Y2.2, Y2.4
unnamed: C4.1, L1.2, L3.1
unnamed: C6.1, L2.2, L4.1
unnamed: C7.1, L3.2, L5.1
unnamed: C8.1, L4.2, L6.1
unnamed: C9.1, L5.2, L7.1
unnamed: C10.1, C12.2, L6.2, L9.1
unnamed: C11.1, L8.2, U2.16
unnamed: C11.2, L7.2
unnamed: C12.1, L10.2, U2.13
unnamed: C13.1, L9.2, L10.1, U2.12
unnamed: C15.1, C17.1, C19.1, C20.1, C21.1, U2.18, U2.20
unnamed: D2.1, R22.1
unnamed: D3.1, R23.1
unnamed: J2.1, L1.1
unnamed: J3.1, L2.1
unnamed: J24.1, Q1.1
unnamed: J25.1, Q2.1
unnamed: L8.1, R1.2
unnamed: Q1.3, R22.2
unnamed: Q2.3, R23.2
unnamed: R2.2, U2.1
unnamed: R3.2, U2.4
unnamed: R4.2, U2.5
unnamed: R5.2, U2.6
unnamed: R6.2, U2.24
unnamed: R7.2, U2.25
unnamed: R8.2, U2.26
unnamed: R9.2, U2.27
unnamed: R10.2, U2.28
unnamed: R12.2, U2.30
unnamed: R13.2, U2.19
unnamed: R16.2, U2.21
unnamed: R17.2, U2.22
unnamed: R18.2, U2.10
unnamed: R19.2, U2.11
unnamed: U2.2, Y1.1
unnamed: U2.3, Y1.2
unnamed: U2.7, Y2.3
unnamed: U2.8, Y2.1
VCC: C1.1, C2.1, D1.1, J1.3, J1.4, U1.3
